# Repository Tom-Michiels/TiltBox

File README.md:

# TiltBox

## Latest version: TiltBox Voice

The custom ESP32-S3 PCB version adds a bottom-facing microphone and voice-generated
games while retaining the 8×8 LED grid and the walnut enclosure style.

- [Hardware, assembly and validation status](hardware/voice-a/README.md)
- [Printable STL files and laser-cut DXF files](hardware/voice-a/mechanical/)
- [KiCad PCB and schematics](hardware/voice-a/pcb/TiltBox-Voice-A.kicad_pro)
- [JLCPCB Gerbers, BOM and placement files](hardware/voice-a/jlcpcb/)
- [Latest firmware source and flashing instructions](firmware/voice-a/README.md)
- [Prebuilt Voice B firmware, 9 October 2026](firmware/voice-a/bin/)
- [Self-hosted voice service and dashboard](cloud/README.md)
- [Publication checks and version provenance](PUBLICATION-2026-10-26.md)

Hardware: electronics **A.3**, enclosure **A.4**, manufacturing package **A.5**.
Software: **Voice B (9 October 2026)**, for the same Voice A PCB; this is not a
new PCB revision. Publication snapshot: 26 October 2026.

These are prototype files, not a claim of production certification. See the
hardware notes for completed checks and outstanding electrical tests. Do not use
the original ESP32-C3 firmware or its wiring instructions for the Voice PCB.

## Original TiltBox (ESP32-C3 / separate modules)

The original files below remain available unchanged. The root `main/`,
`CMakeLists.txt`, `sdkconfig` and the older files directly in `hardware/` belong
to this original version, not TiltBox Voice.

A handheld retro game console with tilt controls, featuring 9 games on an 8x8 LED matrix. Designed at [Maakleerplek](https://maakleerplek.be).

## Bill of Materials

| Component | Quantity | Description | Link |
|-----------|----------|-------------|------|
| ESP32-C3 | 1 | Microcontroller (any ESP32-C3 dev board) | [Amazon](https://www.amazon.de/diymore-ESP32-C3-Development-Supports-Bluetooth/dp/B0DS23ML1L/ref=sr_1_1_sspa?th=1) |
| WS2812 8x8 LED Matrix | 1 | 64 RGB LEDs in 8x8 grid | [Amazon](https://www.amazon.de/CJMCU-8x8-Development-Compatible-Arduino-Raspberry/dp/B0DDPWTH83/ref=sxin_15_pa_sp_search_thematic_sspa) |
| ADXL345 | 1 | 3-axis accelerometer module (I2C) | [Amazon](https://www.amazon.de/APKLVSR-ADXL345-Digital-Accelerating-Transmission/dp/B0CRVL4S54/ref=sr_1_2_sspa) |
| USB Charger Board | 1 | LiPo charging module with protection | [Amazon](https://www.amazon.de/-/en/dp/B09C34TK4F?th=1) |
| LiPo Battery | 1 | 3.7V lithium polymer battery | [Amazon](https://www.amazon.de/-/en/Seamuing-Lithium-Protective-Insulation-Development/dp/B087LTZW61/ref=sr_1_12) |
| Threaded Inserts | 4 | M3x5x7 heat-set inserts for enclosure | [Amazon](https://www.amazon.de/Threaded-RX-M3x5-7-Lead-Free-Bushings-Insertion/dp/B08BCRZZS3/ref=sr_1_1_sspa) |
| M3 Screws | 4 | M3x6mm hex socket button head | [Amazon](https://www.amazon.de/dp/B07ZPTX8B2?ref=ppx_yo2ov_dt_b_fed_asin_title) |
| M3 Screws | 4 | M3x12mm hex socket button head | [Amazon](https://www.amazon.de/dp/B07ZPT7Y9R?ref=ppx_yo2ov_dt_b_fed_asin_title&th=1) |
| Walnut Wood | 1 | 3.2mm x 115x368mm sheet | [Gravierbedarf](https://www.gravierbedarf.de/epages/63201300.sf/en_GB/?ObjectPath=/Shops/63201300/Products/NUSS) |
| Black PLA | 1 | 3D printer filament for enclosure | |
| Jumper wires | 7 | For connections | |

## Wiring

### WS2812 LED Matrix

| WS2812 Pin | ESP32-C3 Pin |
|------------|--------------|
| VCC | 5V |
| GND | GND |
| DIN | GPIO 10 |

### ADXL345 Accelerometer (I2C)

| ADXL345 Pin | ESP32-C3 Pin |
|-------------|--------------|
| VCC | 3.3V |
| GND | GND |
| SDA | GPIO 8 |
| SCL | GPIO 9 |

## Build Instructions

### 1. 3D Printing

Print the enclosure parts in black PLA:

- [tilt_box.stl](hardware/tilt_box.stl) - Main enclosure body
- [tilt box grid.stl](hardware/tilt%20box%20grid.stl) - Grid overlay

[Open in Onshape](https://cad.onshape.com/documents/1ea29db64e579952e6381490/w/44e133dfefb2de18973d13df/e/b5270f9dee790fa11f86224a?renderMode=0&uiState=69ad3dda5e52657494bd1281)

### 2. Laser Cutting

Cut the following from the [wood and plexi.dxf](hardware/wood%20and%20plexi.dxf) file:

- **Walnut wood** (3.2mm thickness): Front frame
- **Clear acrylic/plexi**: Screen cover

### 3. Soldering

Solder the components according to the wiring diagram:

### 4. Screen Assembly

The LED matrix needs a diffuser layer to blend the individual LEDs into a smooth display:

- **Diffuser**: Use a white plastic bag or similar translucent material between the LED matrix and the plexi cover
- **Optional darkening**: Adding a dark PVC film (e.g. available at Lukas Creative) provides additional darkness to the screen, improving contrast

### 5. Final Assembly

1. Insert the M3x5x7 threaded inserts into the 3D printed enclosure using a soldering iron
2. Mount all electronics inside the enclosure
3. Stack the layers: LED matrix -> diffuser -> (optional dark film) -> plexi -> walnut frame
4. Secure with M3x6mm screws (front) and M3x12mm screws (back)

## Games

Switch between games by flipping the board upside down.

### 1. Maze
Navigate a ball through a randomly generated maze. Tilt to move the yellow ball to the red goal. A rainbow animation plays when you win.

### 2. Ball Trail
A simple ball that leaves a fading trail as it moves. Tilt to control direction.

### 3. Glow Ball
A glowing ball with a smooth gradient effect that follows your tilt movements.

### 4. Snake
Classic snake game. Tilt to change direction and eat the red food to grow. Don't hit yourself!

### 5. Breakout
Break the colored bricks at the top with a bouncing ball. Tilt left/right to move the paddle.

### 6. Dodge
Avoid falling obstacles. Tilt left/right to move your player at the bottom. Score increases as obstacles pass.

### 7. Scroll Text
Displays scrolling text: "maakleerplek"

### 8. Animation
Cycles through animated patterns:
- Spiral rainbow
- Wave
- Rainbow gradient

### 9. Tetris
Classic falling block game. Tilt left/right to move pieces, tilt forward to rotate, tilt backward for fast drop.

## Building and Flashing

Requires ESP-IDF v4.3+.

```bash
# Source ESP-IDF environment
source ~/esp/esp-idf/export.sh

# Build
idf.py build

# Flash
idf.py flash

# Monitor serial output
idf.py monitor
```

## Controls

- **Tilt**: Move/control in all games
- **Flip board**: Switch to next game
- **Keep level during startup**: Calibrates the accelerometer

## Display Format

The WS2812 LEDs use GRB color format. Pixels are addressed row by row, 0-63.

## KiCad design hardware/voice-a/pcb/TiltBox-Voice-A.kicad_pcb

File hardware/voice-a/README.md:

# TiltBox Voice hardware

Publication snapshot: **26 October 2026**. Electronics **A.3**, enclosure **A.4**,
manufacturing package **A.5**. Firmware **Voice B** runs on this same board.

## Files to use

| Purpose | Files |
| --- | --- |
| 3D print | [body](mechanical/TiltBox-Voice-A-body.stl), [grid](mechanical/TiltBox-Voice-A-grid.stl), [button](mechanical/TiltBox-Voice-A-button.stl) |
| Laser-cut 3 mm walnut | [walnut DXF](mechanical/TiltBox-Voice-A-walnut-3mm.dxf) |
| Laser-cut 3 mm dark grey smoked PMMA | [PMMA DXF](mechanical/TiltBox-Voice-A-smoked-plexi-3mm.dxf) |
| Combined laser layout | [wood and PMMA DXF](mechanical/TiltBox-Voice-A-wood-and-plexi.dxf) |
| Hand-cut diffuser / filter | [SVG template](mechanical/diffuser-manual-cut.svg) |
| Editable electronics | [KiCad project](pcb/TiltBox-Voice-A.kicad_pro), [PCB](pcb/TiltBox-Voice-A.kicad_pcb), [schematic](pcb/TiltBox-Voice-A.kicad_sch) |
| JLCPCB fabrication | [Gerber ZIP](jlcpcb/TiltBox-Voice-A-Gerbers.zip) |
| JLCPCB assembly | [BOM](jlcpcb/BOM.csv), [CPL](jlcpcb/CPL.csv) |
| Assembly / ordering guides (Dutch) | [Assembly](jlcpcb/Assemblage.pdf), [ordering and checks](jlcpcb/Bestellen-en-controle.pdf) |
| Schematic PDF | [Schema.pdf](reports/Schema.pdf) |
| Firmware | [Source and instructions](../../firmware/voice-a/README.md) |

The combined DXF is an alternative layout, not an additional set of parts.
Files in `mechanical/reference/` are original inputs for the generation scripts,
not the Voice parts to print. Units are millimetres. Measure actual sheet
thickness and calibrate laser kerf before cutting the final parts.

## Design

- 78 × 78 mm, 1.6 mm, four-layer PCB, 64 WS2812B-V5 RGB LEDs.
- ESP32-S3-WROOM-1U-N16R8; attach the external antenna before radio tests.
- LSM6DS3TR-C IMU and ICS-43434 bottom-port I2S microphone.
- USB-C programming and power, BQ25185 power-path charger, edge sleep/wake button.
- R20/R21 are 1 MΩ each. Firmware configures the IMU interrupt idle-high.
- No separate per-LED C1–C64 capacitors; other supply decoupling remains.

## Enclosure and battery

Walnut and PMMA are **3 mm** thick. Print the upper grid in opaque black material
to absorb stray light. The paper/dark translucent filter stack is **0.2 mm total**,
90 × 90 mm including the rim, with the eight mounting holes from the SVG. It has
no cut-outs over the LED cells. **Never laser-cut PVC.**

Use eight ISO 7380-1 **M3×14** screws above and eight **M3×6** screws at the sides.
The vertical insert pilot holes in the printed body are **4 mm**; match the actual
heat-set inserts to the material and check a test coupon before assembly.

Battery: protected **1S LiPo, 3.7 V nominal / 4.2 V charging**, with **JST-PH 2-pin,
2.0 mm pitch (PHR-2)** cable connector. PCB J2 **pin 1 is VBAT+**, **pin 2 is GND−**.
Identical-looking battery plugs can have reversed polarity: verify before connecting.
The charger is configured for approximately 300 mA; the cell must permit this
charge current, and the original assembly specification calls for ≥2 A discharge.
TH1 must be thermally coupled to the cell, with suitable electrical insulation.

The enclosure CAD retains the original nominal **45 × 26 × 5 mm** pack envelope.
A MakerFocus 1000 mAh pack was used in subsequent functional battery tests; that
does **not** establish its fit in the closed enclosure or all of its electrical
ratings. Do not assume arbitrary 1000 mAh packs fit these STL files.

## Validation and limitations

The included manufacturing files are the existing prototype release, not a new
PCB layout. Archived KiCad release checks report zero DRC/ERC violations and no
unconnected items; their dates remain visible in the JSON reports. Fresh DRC
(including schematic parity) and ERC checks on 26 October also returned zero
violations; see `reports/*publication-2026-10-26.json`. These checks
do not establish electrical safety or eliminate the need for fabrication review.

On the first assembled board (2 October 2026), the 64 LEDs, IMU/self-test,
microphone data, PSRAM test, passive Wi-Fi scan, USB-C in both orientations,
tilt directions and button sleep/wake were checked. On 3 October, the owner
confirmed operation on battery, sleep/wake and a cool battery. Seven USB ADC
readings over about 78 seconds ranged from 3.958 to 3.966 V; these are firmware
readings, not calibrated multimeter measurements. USB reconnection after sleep
needed an off/on cycle during that session; the cause was not established.

The 9 October firmware notes report target interpreter/IMU/USB tests and local
mock-cloud tests. Earlier hardware results must not be treated as a full
regression test of every behaviour in this newer firmware.

Still outstanding: measured charging and sleep currents, charger termination and
thermal protection, supply behaviour under peak load, calibrated ADC accuracy,
closed-enclosure fit/RF/thermal tests and full paid voice-service integration.
Before ordering, reconfirm JLCPCB stack-up, impedance assumptions, component
availability and assembly orientation. This is a prototype, not certified hardware.

## Mechanical source

`tools/build_enclosure.py`, `build_wood.py`, `build_accessories.py`, `design.py`
and `mechanical_spec.py` preserve the source used for the generated geometry.
They require Python with numpy, scipy, trimesh, manifold3d, shapely, triangle,
matplotlib and ezdxf. Run enclosure, then wood, then accessories in a disposable
copy: these scripts overwrite generated mechanical
outputs. The released STL/DXF files above are the manufacturing snapshot.

The routed KiCad project is authoritative for the PCB; these mechanical helper
scripts are not a PCB routing/release pipeline.

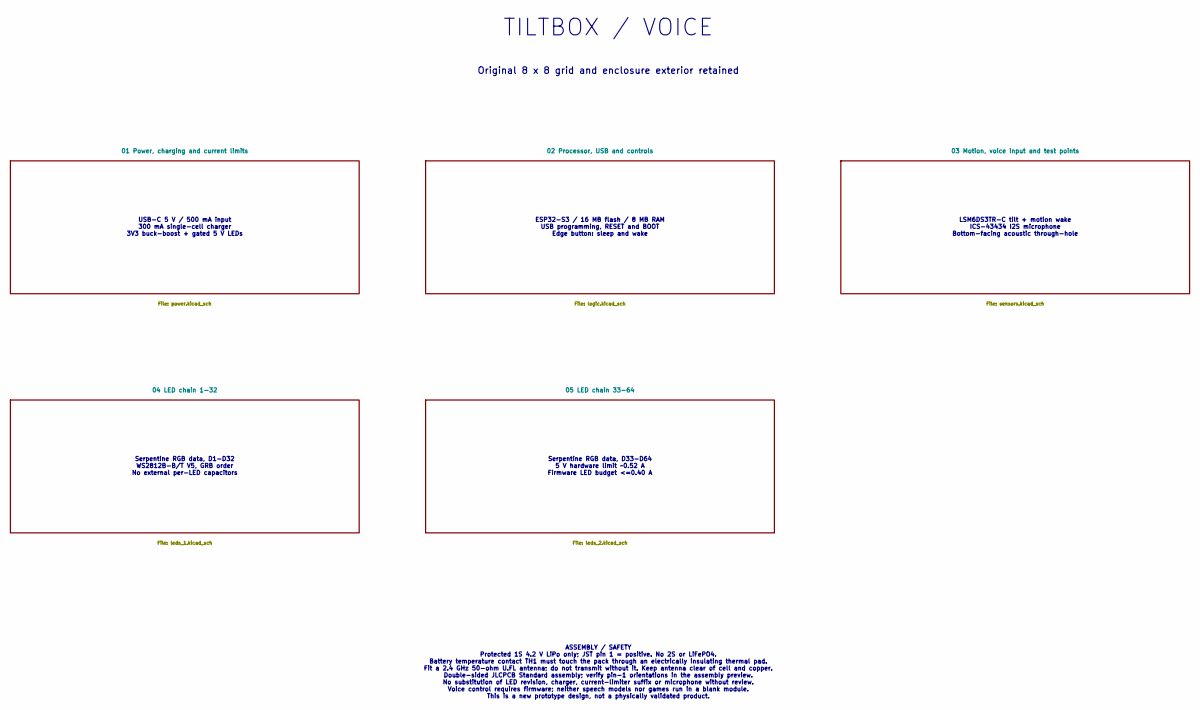
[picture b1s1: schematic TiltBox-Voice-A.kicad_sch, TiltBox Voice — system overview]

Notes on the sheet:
TILTBOX / VOICE
Original 8 x 8 grid and enclosure exterior retained
USB-C 5 V / 500 mA input 300 mA single-cell charger 3V3 buck-boost + gated 5 V LEDs
ESP32-S3 / 16 MB flash / 8 MB RAM USB programming, RESET and BOOT Edge button: sleep and wake
LSM6DS3TR-C tilt + motion wake ICS-43434 I2S microphone Bottom-facing acoustic through-hole
Serpentine RGB data, D1-D32 WS2812B-B/T V5, GRB order No external per-LED capacitors
Serpentine RGB data, D33-D64 5 V hardware limit ~0.52 A Firmware LED budget <=0.40 A
ASSEMBLY / SAFETY Protected 1S 4.2 V LiPo only; JST pin 1 = positive. No 2S or LiFePO4. Battery temperature contact TH1 must touch the pack through an electrically insulating thermal pad. Fit a 2.4 GHz 50-ohm U.FL antenna; do not transmit without it. Keep antenna clear of cell and copper. Double-si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

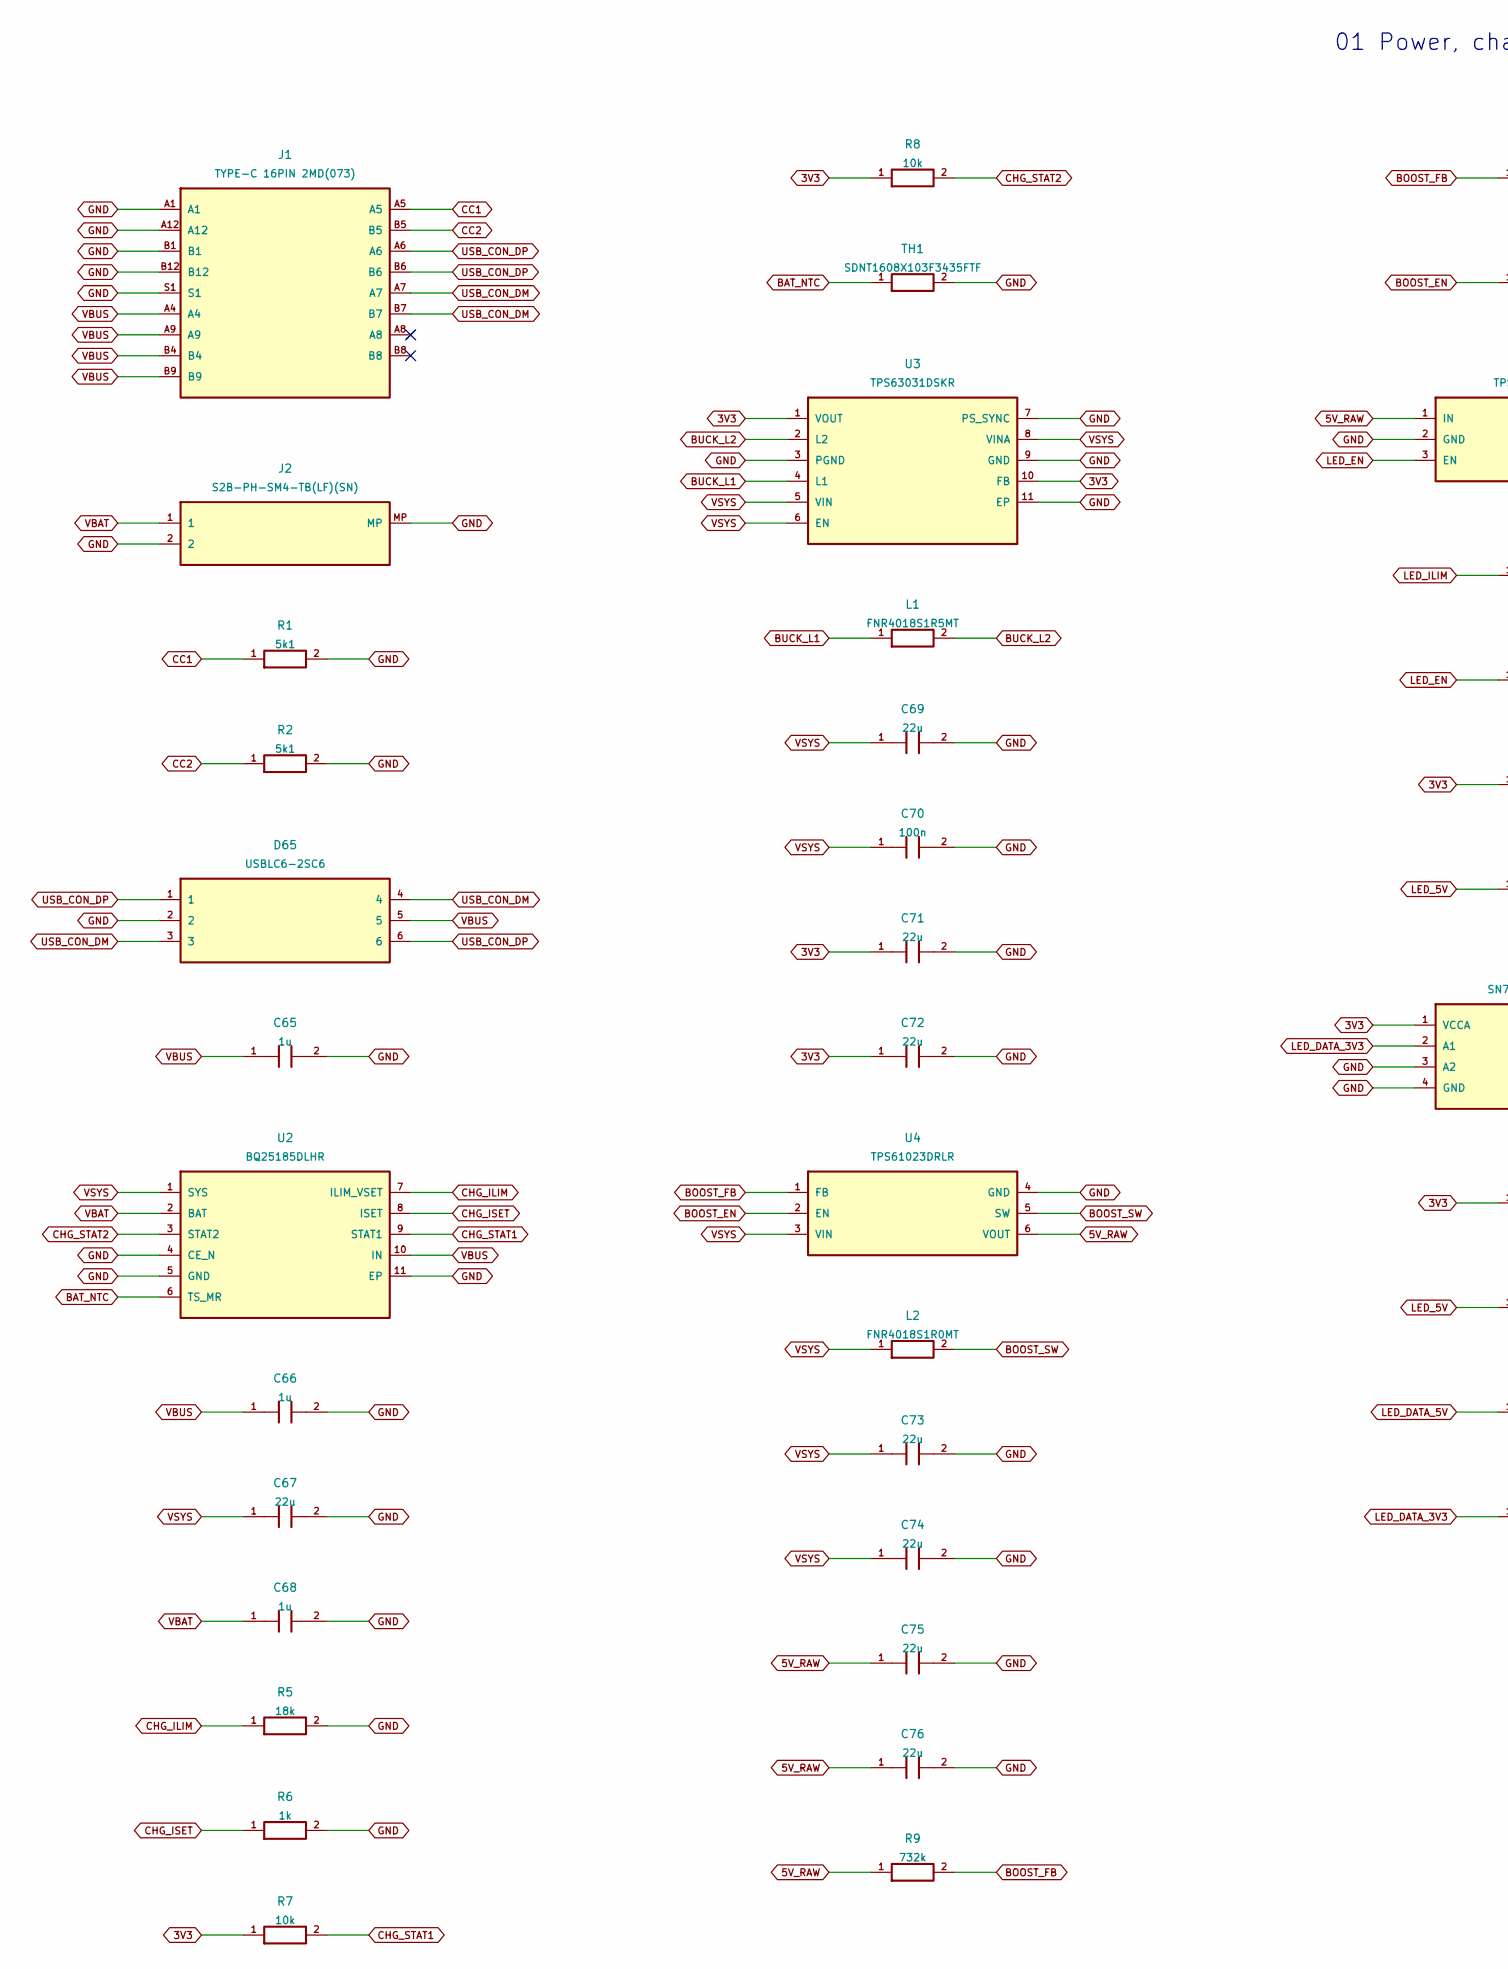
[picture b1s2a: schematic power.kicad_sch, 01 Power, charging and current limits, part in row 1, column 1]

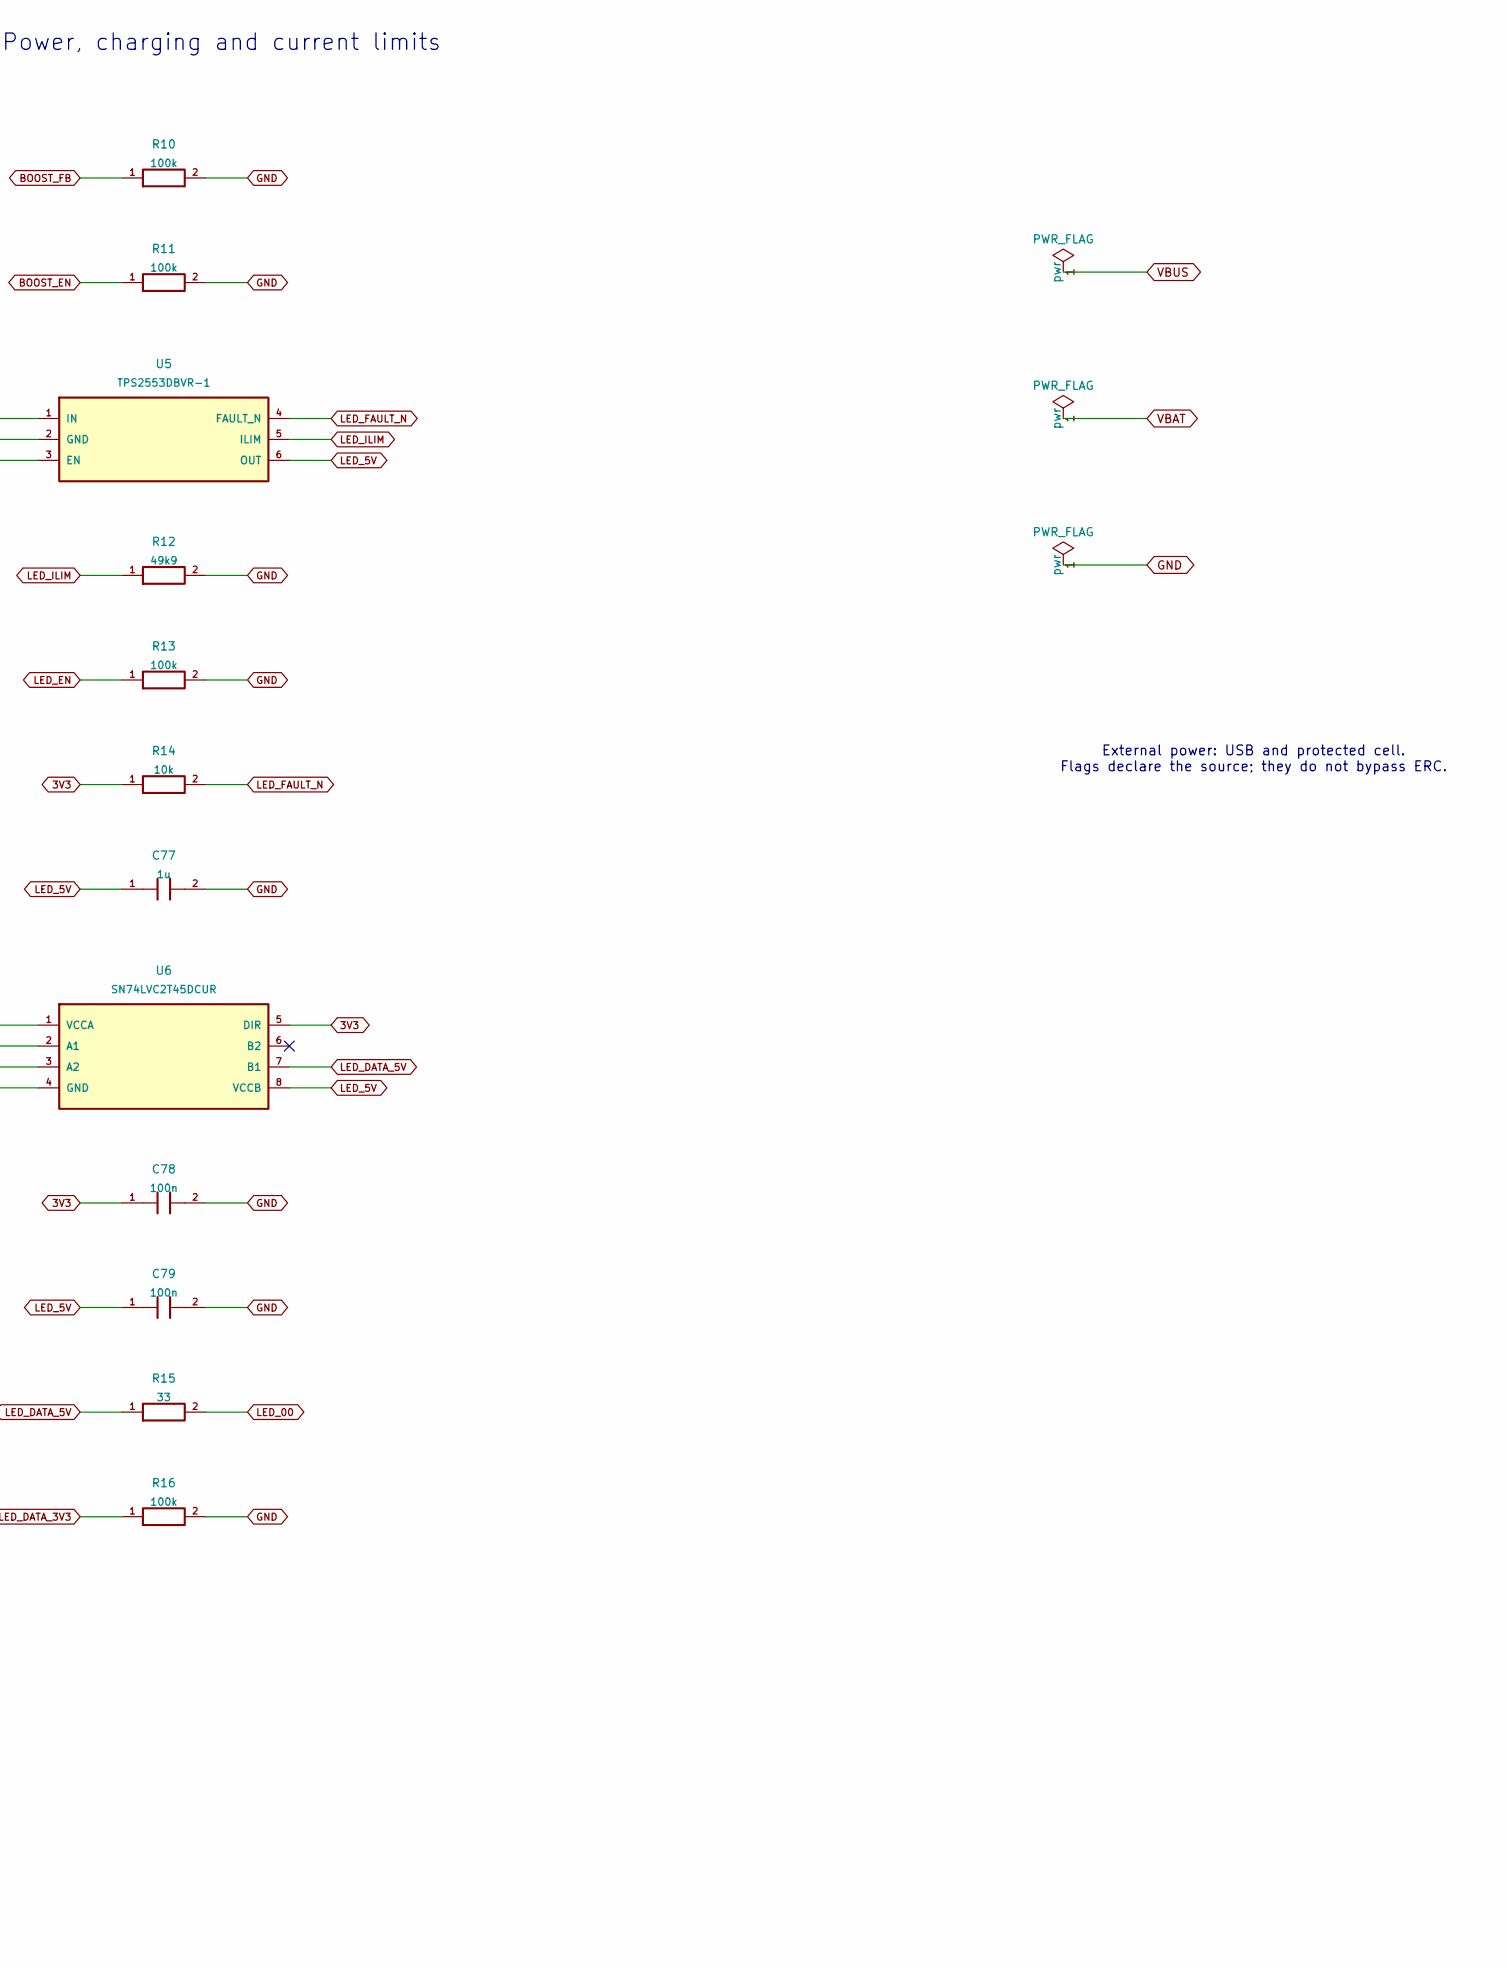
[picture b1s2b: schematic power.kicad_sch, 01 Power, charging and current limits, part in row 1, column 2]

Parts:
C65, C66, C68, C77: 1u; C_0603_1608Metric; LCSC Part C15849
C67, C69, C71, C72, C73, C74, C75, C76: 22u; C_0805_2012Metric; LCSC Part C45783
C70, C78, C79: 100n; C_0402_1005Metric; LCSC Part C1525
D65: USBLC6-2SC6; SOT-23-6; LCSC Part C2687116
J1: TYPE-C 16PIN 2MD(073); USB_C_Receptacle_HCTL_HC-TYPE-C-16P-01A; LCSC Part C2765186
J2: S2B-PH-SM4-TB(LF)(SN); JST_PH_S2B-PH-SM4-TB_1x02-1MP_P2.00mm_Horizontal; LCSC Part C295747
L1: FNR4018S1R5MT; L_Changjiang_FNR4018S; LCSC Part C167802
L2: FNR4018S1R0MT; L_Changjiang_FNR4018S; LCSC Part C167801
R1, R2: 5k1; R_0402_1005Metric; LCSC Part C25905
R5: 18k; R_0402_1005Metric; LCSC Part C25762
R6: 1k; R_0402_1005Metric; LCSC Part C11702
R7, R8, R14: 10k; R_0402_1005Metric; LCSC Part C25744
R9: 732k; R_0402_1005Metric; LCSC Part C27016
R10, R11, R13, R16: 100k; R_0402_1005Metric; LCSC Part C25741
R12: 49k9; R_0402_1005Metric; LCSC Part C25897
R15: 33; R_0402_1005Metric; LCSC Part C25105
TH1: SDNT1608X103F3435FTF; R_0603_1608Metric; LCSC Part C525660
U2: BQ25185DLHR; Texas_DLH0010A_WSON-10-1EP_2.2x2mm_P0.4mm_EP0.9x1.5mm; LCSC Part C19725033
U3: TPS63031DSKR; WSON-10-1EP_2.5x2.5mm_P0.5mm_EP1.2x2mm; LCSC Part C15516
U4: TPS61023DRLR; SOT-563; LCSC Part C919459
U5: TPS2553DBVR-1; SOT-23-6; LCSC Part C111738
U6: SN74LVC2T45DCUR; VSSOP-8_2.3x2mm_P0.5mm; LCSC Part C15741

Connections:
3V3: C71.1, C72.1, C78.1, R7.1, R8.1, R14.1, U3.1 (VOUT), U3.10 (FB), U6.1 (VCCA), U6.5 (DIR); also elsewhere on the board
5V_RAW: C75.1, C76.1, R9.1, U4.6 (VOUT), U5.1 (IN); also elsewhere on the board
BAT_NTC: TH1.1, U2.6 (TS_MR); also elsewhere on the board
BOOST_EN: R11.1, U4.2 (EN); also elsewhere on the board
BOOST_FB: R9.2, R10.1, U4.1 (FB)
BOOST_SW: L2.2, U4.5 (SW)
BUCK_L1: L1.1, U3.4 (L1)
BUCK_L2: L1.2, U3.2 (L2)
CC1: J1.A5, R1.1
CC2: J1.B5, R2.1
CHG_ILIM: R5.1, U2.7 (ILIM_VSET)
CHG_ISET: R6.1, U2.8 (ISET)
CHG_STAT1: R7.2, U2.9 (STAT1); also elsewhere on the board
CHG_STAT2: R8.2, U2.3 (STAT2); also elsewhere on the board
GND: C65.2, C66.2, C67.2, C68.2, C69.2, C70.2, C71.2, C72.2, C73.2, C74.2, C75.2, C76.2, C77.2, C78.2, C79.2, D65.2, J1.A1, J1.A12, J1.B1, J1.B12, J1.S1, J2.2, J2.MP, R1.2, R2.2, R5.2, R6.2, R10.2, R11.2, R12.2, R13.2, R16.2, TH1.2, U2.4 (CE_N), U2.5 (GND), U2.11 (EP), U3.3 (PGND), U3.7 (PS_SYNC), U3.9 (GND), U3.11 (EP), U4.4 (GND), U5.2 (GND), U6.3 (A2), U6.4 (GND); also elsewhere on the board
LED_00: R15.2; also elsewhere on the board
LED_5V: C77.1, C79.1, U5.6 (OUT), U6.8 (VCCB); also elsewhere on the board
LED_DATA_3V3: R16.1, U6.2 (A1); also elsewhere on the board
LED_DATA_5V: R15.1, U6.7 (B1)
LED_EN: R13.1, U5.3 (EN); also elsewhere on the board
LED_FAULT_N: R14.2, U5.4 (FAULT_N); also elsewhere on the board
LED_ILIM: R12.1, U5.5 (ILIM)
USB_CON_DM: D65.3, D65.4, J1.A7, J1.B7; also elsewhere on the board
USB_CON_DP: D65.1, D65.6, J1.A6, J1.B6; also elsewhere on the board
VBAT: C68.1, J2.1, U2.2 (BAT); also elsewhere on the board
VBUS: C65.1, C66.1, D65.5, J1.A4, J1.A9, J1.B4, J1.B9, U2.10 (IN); also elsewhere on the board
VSYS: C67.1, C69.1, C70.1, C73.1, C74.1, L2.1, U2.1 (SYS), U3.5 (VIN), U3.6 (EN), U3.8 (VINA), U4.3 (VIN); also elsewhere on the board

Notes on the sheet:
01 Power, charging and current limits
External power: USB and protected cell. Flags declare the source; they do not bypass ERC.

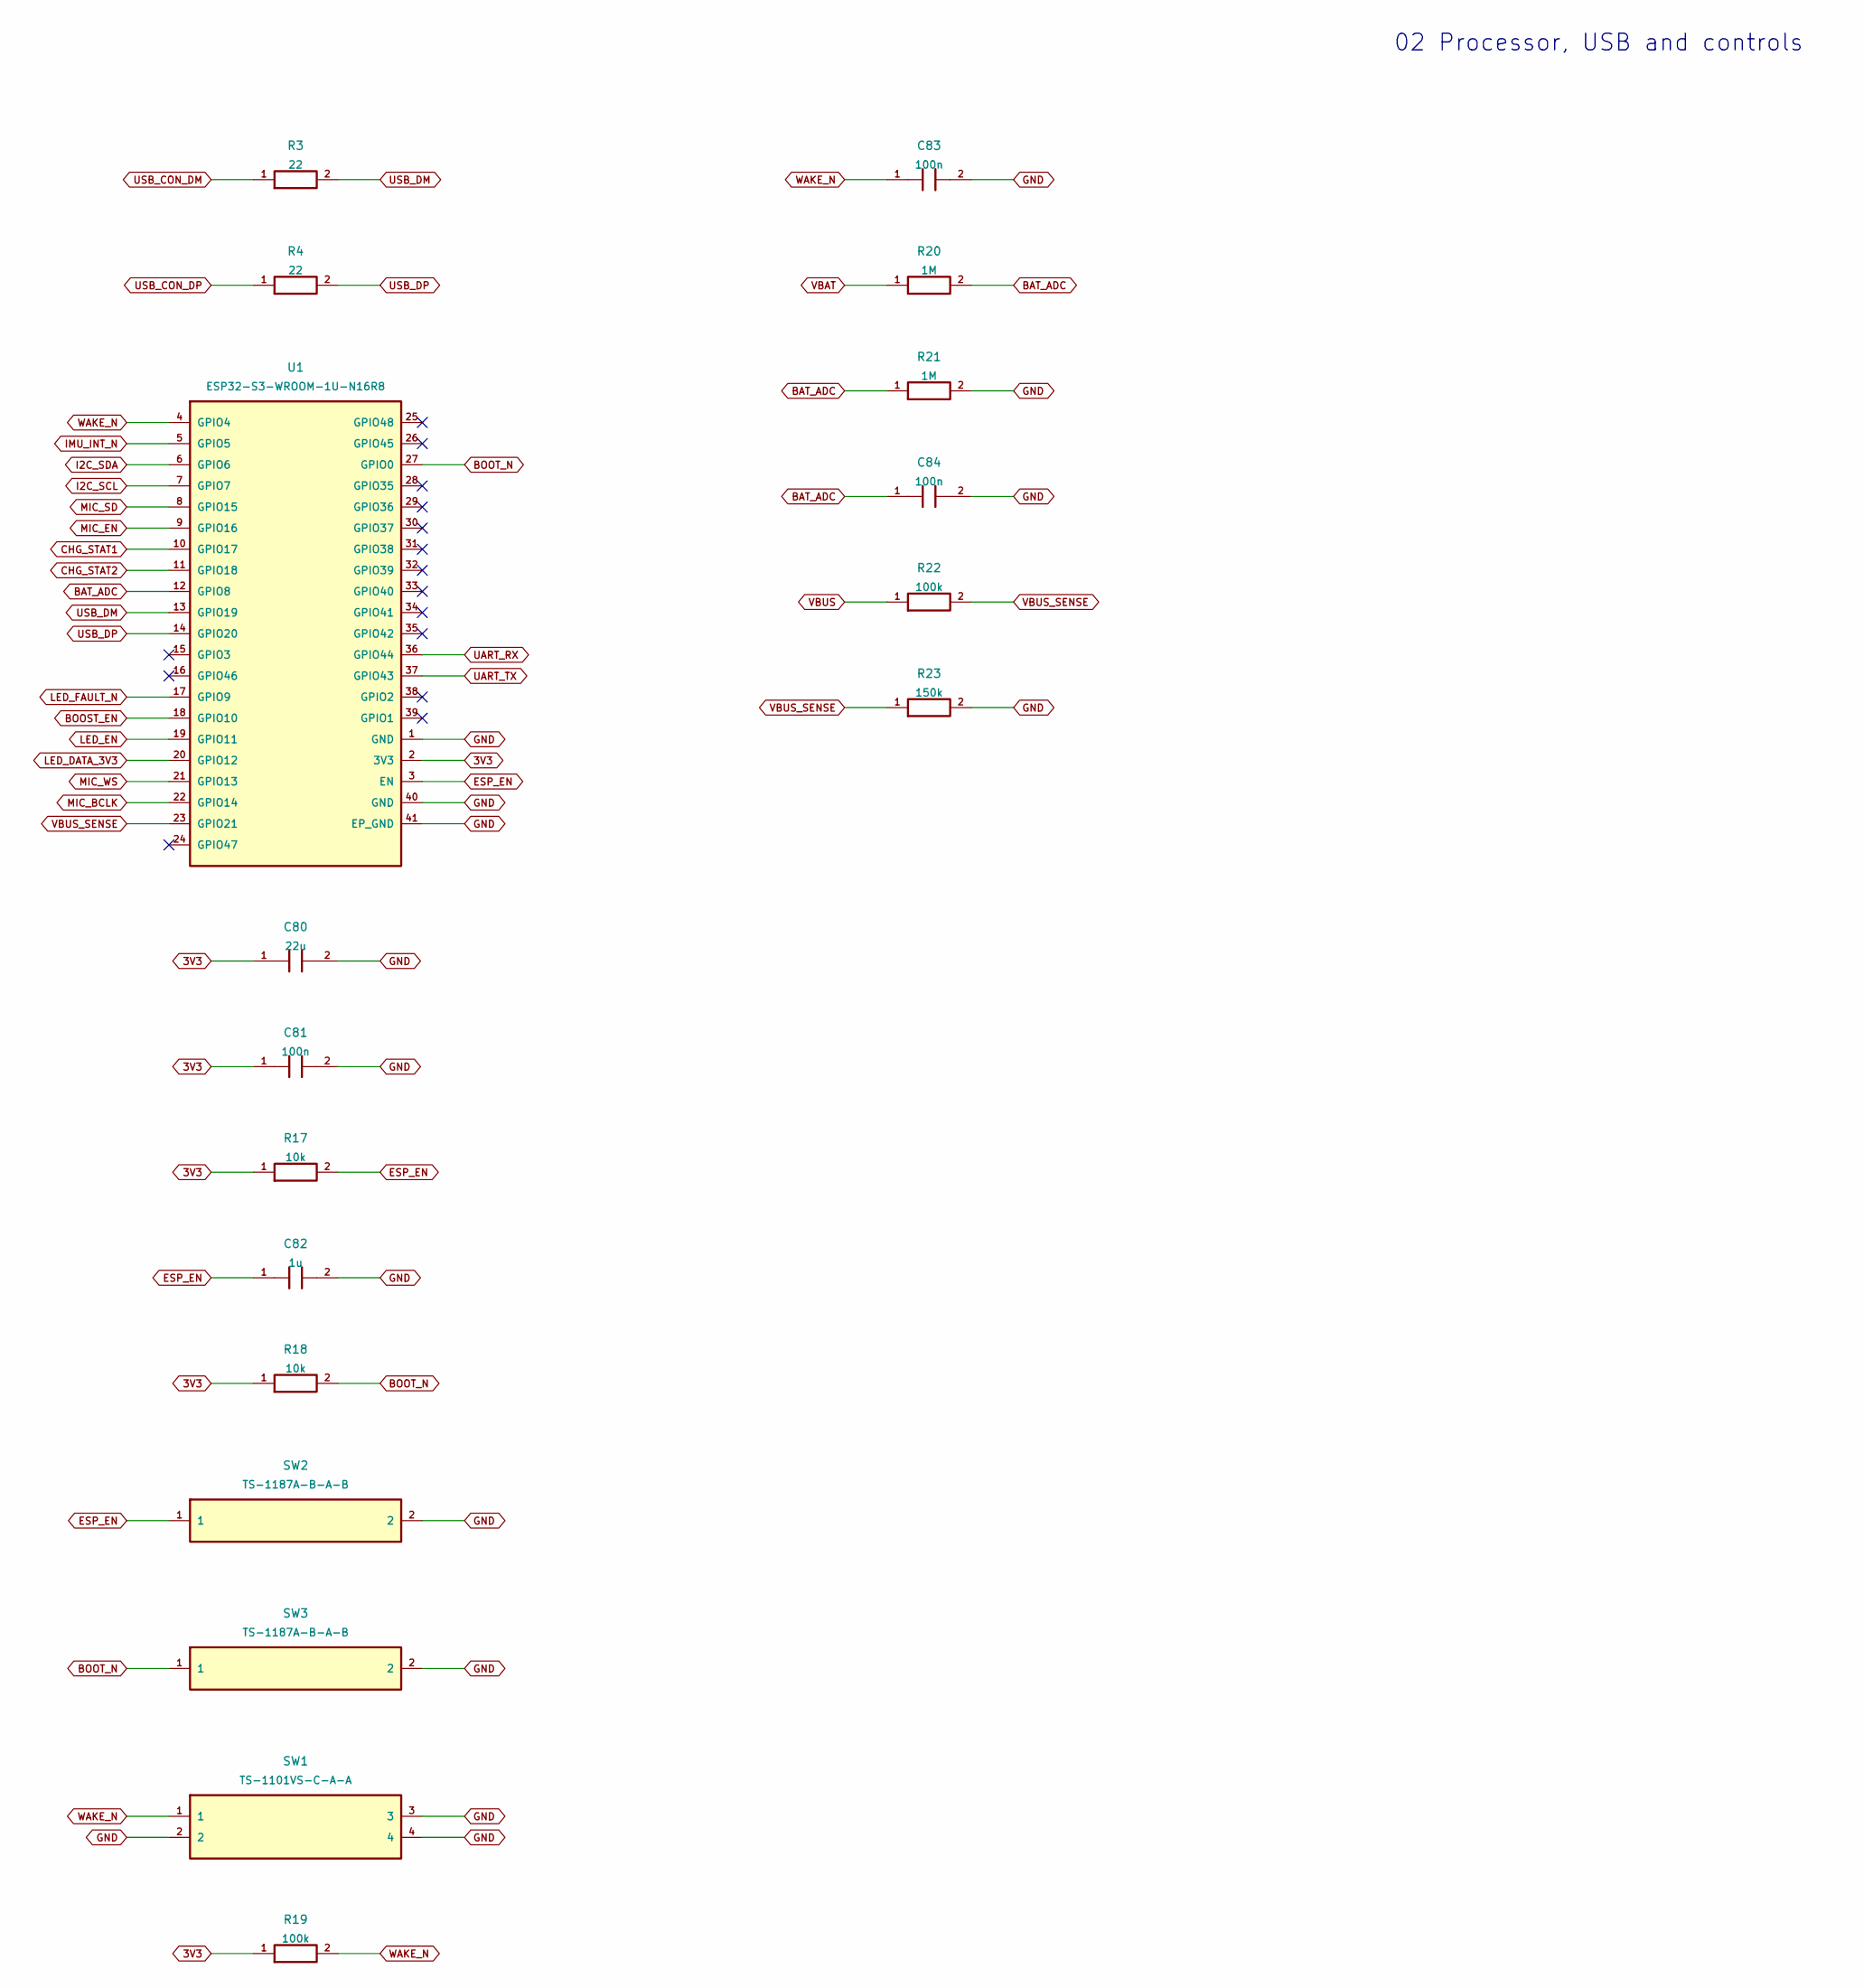
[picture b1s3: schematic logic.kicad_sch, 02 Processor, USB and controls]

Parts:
C80: 22u; C_0805_2012Metric; LCSC Part C45783
C81, C83, C84: 100n; C_0402_1005Metric; LCSC Part C1525
C82: 1u; C_0603_1608Metric; LCSC Part C15849
R3, R4: 22; R_0402_1005Metric; LCSC Part C25092
R17, R18: 10k; R_0402_1005Metric; LCSC Part C25744
R19, R22: 100k; R_0402_1005Metric; LCSC Part C25741
R20, R21: 1M; R_0402_1005Metric; LCSC Part C26083
R23: 150k; R_0402_1005Metric; LCSC Part C25755
SW1: TS-1101VS-C-A-A; KEY-SMD_TS-1101VS-C-A-A; LCSC Part C318936
SW2, SW3: TS-1187A-B-A-B; SW_Push_1P1T_XKB_TS-1187A; LCSC Part C318884
U1: ESP32-S3-WROOM-1U-N16R8; ESP32-S3-WROOM-1U; LCSC Part C3013946

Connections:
3V3: C80.1, C81.1, R17.1, R18.1, R19.1, U1.2 (3V3); also elsewhere on the board
BAT_ADC: C84.1, R20.2, R21.1, U1.12 (GPIO8)
BOOST_EN: U1.18 (GPIO10); also elsewhere on the board
BOOT_N: R18.2, SW3.1, U1.27 (GPIO0); also elsewhere on the board
CHG_STAT1: U1.10 (GPIO17); also elsewhere on the board
CHG_STAT2: U1.11 (GPIO18); also elsewhere on the board
ESP_EN: C82.1, R17.2, SW2.1, U1.3 (EN); also elsewhere on the board
GND: C80.2, C81.2, C82.2, C83.2, C84.2, R21.2, R23.2, SW1.2, SW1.3, SW1.4, SW2.2, SW3.2, U1.1 (GND), U1.40 (GND), U1.41 (EP_GND); also elsewhere on the board
I2C_SCL: U1.7 (GPIO7); also elsewhere on the board
I2C_SDA: U1.6 (GPIO6); also elsewhere on the board
IMU_INT_N: U1.5 (GPIO5); also elsewhere on the board
LED_DATA_3V3: U1.20 (GPIO12); also elsewhere on the board
LED_EN: U1.19 (GPIO11); also elsewhere on the board
LED_FAULT_N: U1.17 (GPIO9); also elsewhere on the board
MIC_BCLK: U1.22 (GPIO14); also elsewhere on the board
MIC_EN: U1.9 (GPIO16); also elsewhere on the board
MIC_SD: U1.8 (GPIO15); also elsewhere on the board
MIC_WS: U1.21 (GPIO13); also elsewhere on the board
UART_RX: U1.36 (GPIO44); also elsewhere on the board
UART_TX: U1.37 (GPIO43); also elsewhere on the board
USB_CON_DM: R3.1; also elsewhere on the board
USB_CON_DP: R4.1; also elsewhere on the board
USB_DM: R3.2, U1.13 (GPIO19)
USB_DP: R4.2, U1.14 (GPIO20)
VBAT: R20.1; also elsewhere on the board
VBUS: R22.1; also elsewhere on the board
VBUS_SENSE: R22.2, R23.1, U1.23 (GPIO21)
WAKE_N: C83.1, R19.2, SW1.1, U1.4 (GPIO4)

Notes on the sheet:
02 Processor, USB and controls
